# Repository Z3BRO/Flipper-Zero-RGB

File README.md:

# ARCHIVED

Hello everyone! Z3BRO here. It is with great sadness I have to come forward and say that my Flipper Zero RGB Repositories are now dead. 
Instead of dwelling on the fact that its over, I want to thank all the wonderful people who helped me progress as far as I did.

To Rabbitt and Foxx, thank you for your unwavering support through my entire Flipper Zero journey. 
Although it didn't end like we all wished it could have, you will both forever have a special place in my heart. 

To Astro, thank you for everything you did. You know what I'm talking about, thank you for that. I will forever be in your debt. 

To CodeAllNight, thank you for taking this stupid project of mine to the next level. Your selfless acts were not disregarded. 

To the Flipper Zero team, thank you for all your hard work with the Flipper Zero development and the incredible community you've built. 

And finally, I thank all of you! Without the community's support, I would never have been able to do any of this. Thank you. 

# The Future of my RGB Mods

Unfortunately, as you all know, unfortunate circumstances resulted in the termination of my partnership with Rabbit-Labs and the stopping of production. 

But do not fret. I have decided to fully release all the PCB Design Files to my final Internal-RGB and Z3BRgb boards. The KiCad files will be in this repository. 
After some heavy Internal-RGB testing, I made countless changes to the design. These changes eliminate all of the issues with V1 of Internal-RGB and add some new features.

I have removed all licenses from these boards, feel free to distribute, modify, produce and or sell them at your discretion. 

# Flipper Zero RGB

    Big thanks to Quenon#1989, t.me/hitriy, axum#6461, and codeallnight#1337 for making this possible!
This repo is the complilation of all the information avaliable on the Flipper Zero RGB Mods.
# RGB Backlight
Here you can find all the information on the RGB Backlight Mod for the Flipper Zero

## Showcase Video 
- [YouTube](https://youtu.be/W1frMyVFv6Y)
## RGB Backlight Parts

- Capacitors (0.1uF 0603):
  - [Digikey](https://www.digikey.com/en/products/detail/kyocera-avx/06036C104JAT2A/1600414)
- LEDs (SK6805-EC 15):
  - [Digikey](https://www.digikey.com/en/products/detail/adafruit-industries-llc/4492/11569136)
  - [Adafruit](https://www.adafruit.com/product/4492)
  - [Mouser](https://mouser.com/ProductDetail/Adafruit/4492?qs=CUBnOrq4ZJz3oeplDXDOWA%3D%3D)
  - [AliExpress](https://www.aliexpress.us/item/2251832771718100.html)
- Thin gauge wire (36 AWG):
  - [AliExpress](https://www.aliexpress.us/item/3256805268543019.html)

For each Module, you need 3 Capacitors and 3 LEDs

When purchasing Backlight PCBs, ensure the thickness is set to 0.6mm and the layer amount is set to 2.

## Install Guides

- [Updated Guide by Z3BRO](https://github.com/Z3BRO/Flipper-Zero-RGB/blob/main/InternalRGBInstalGuide.md) 

Outdated guides

- [Video Guide by Z3BRO](https://youtu.be/pft1CI5ikA4)
- [Guide by t.me/hitriy](https://telegra.ph/Flipper-Zero-RGB-backlight-guide-12-26)
- [LED Backlight Board Removal Tutorial (Russian)](https://telegra.ph/Izmenenie-cveta-podsvetki-Flipper-Zero-11-14) - Translation may be needed.

## RGB Backlight PCB Assembly

- [Assembly Video](https://youtu.be/N64fDjziTaE)

# Internal RGB
Internal RGB For the Flipper Zero is a mod I have been working on for about a year now.

This mod is for people with a Transparent/Translucent Shell that want their Flippers to be a glowing beacon of light for the Flipper Gods, or they just wanna let you know that their Flipper is cooler than yours because it has gamer lights.

## Where to purchase
The Internal-RGB mod is no longer officially sold nor produced by me. After making these boards open source, people may begin to manufacture and sell them. 

## Supporting Mods
The first batch of Internal RGB Mods will require the user to solder a wire to a Vibro test pad or to the Data Out pad of RGB Backlights that have it (Not all RGB Backlights have a Data Out pad, those that do not are not compatiable with Internal RGB). 

After I placed the order for a production run of Internal RGB I noticed there was a Vibro test pad on the RFID/NFC PCB underneath the mod, on future releases of Internal RGB you will have to option to do a completley wireless install (you will still have to solder the Internal RGB PCB to the RFID/NFC PCB, you just wont need any wires). 

Please note that if you would like to use an RGB Backlight along side your Internal RGB you MUST solder a wire from the RGB Backlight's Data Out pad to the Internal RGB's Data In pad, connecting both the RGB Backlight and Internal RGB to the Vibro line WILL result in issues when changing the color of the LEDs.

## How to install
- [Internal RGB Instal Guide](https://github.com/Z3BRO/Flipper-Zero-RGB/blob/main/InternalRGBInstalGuide.md)

# Supported Firmwares

All repositories below support the RGB Backlight Mod. Only the community modified OFW Supports Internal RGB as of right now.

- **Community Modified**:
  - [OFW (With Internal RGB Support!)](https://github.com/Z3BRO/Flipper-Zero-OFW-RGB)

- **Natively Supported**:
  - [Momentum Firmware](https://github.com/Next-Flip/Momentum-Firmware)
  - [Unleashed Firmware (RGB Specific Build)](https://github.com/DarkFlippers/unleashed-firmware)
  - [RougeMaster Firmware](https://github.com/RogueMaster/flipperzero-firmware-wPlugins)
  - [Xtreme Firmware](https://github.com/Flipper-XFW/Xtreme-Firmware)

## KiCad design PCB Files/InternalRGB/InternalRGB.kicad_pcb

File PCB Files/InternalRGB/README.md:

When ordering, set layer count to 2 and thickness to 0.1mm. Make sure you are ordering Flex PCBs.

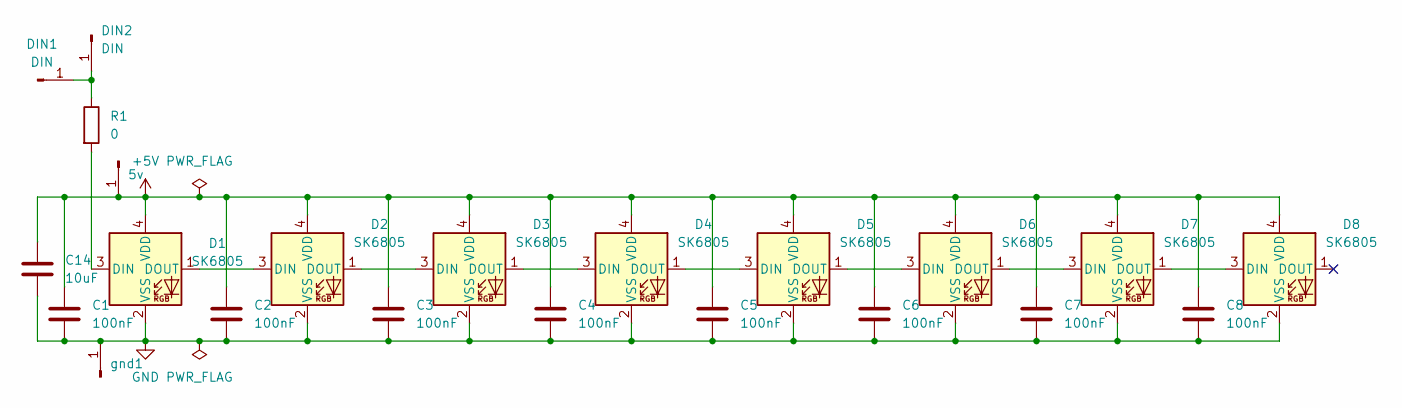
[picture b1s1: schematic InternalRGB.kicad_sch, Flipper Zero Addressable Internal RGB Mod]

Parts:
5v1: 5v; PinHeader_1x01_P2.54mm_Vertical
C1, C2, C3, C4, C5, C6, C7, C8: 100nF; C_0402_1005Metric
C14: 10uF; C_0402_1005Metric
D1, D2, D3, D4, D5, D6, D7, D8: SK6805; LED_SK6812_EC15_1.5x1.5mm
DIN1: DIN; SolderWirePad_1x01_SMD_1x2mm
DIN2: DIN; PinHeader_1x01_P2.54mm_Vertical
R1: 0; R_0402_1005Metric
gnd1: gnd; PinHeader_1x01_P2.54mm_Vertical

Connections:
+5V: 5v1.1, C1.1, C2.1, C3.1, C4.1, C5.1, C6.1, C7.1, C8.1, C14.1, D1.4 (VDD), D2.4 (VDD), D3.4 (VDD), D4.4 (VDD), D5.4 (VDD), D6.4 (VDD), D7.4 (VDD), D8.4 (VDD)
GND: C1.2, C2.2, C3.2, C4.2, C5.2, C6.2, C7.2, C8.2, C14.2, D1.2 (VSS), D2.2 (VSS), D3.2 (VSS), D4.2 (VSS), D5.2 (VSS), D6.2 (VSS), D7.2 (VSS), D8.2 (VSS), gnd1.1; also elsewhere on the board
unnamed: D1.3 (DIN), R1.2
unnamed: D1.1 (DOUT), D2.3 (DIN)
unnamed: D2.1 (DOUT), D3.3 (DIN)
unnamed: D3.1 (DOUT), D4.3 (DIN)
unnamed: D4.1 (DOUT), D5.3 (DIN)
unnamed: D5.1 (DOUT), D6.3 (DIN)
unnamed: D6.1 (DOUT), D7.3 (DIN)
unnamed: D7.1 (DOUT), D8.3 (DIN)
unnamed 10: DIN1.1, DIN2.1, R1.1; also elsewhere on the board

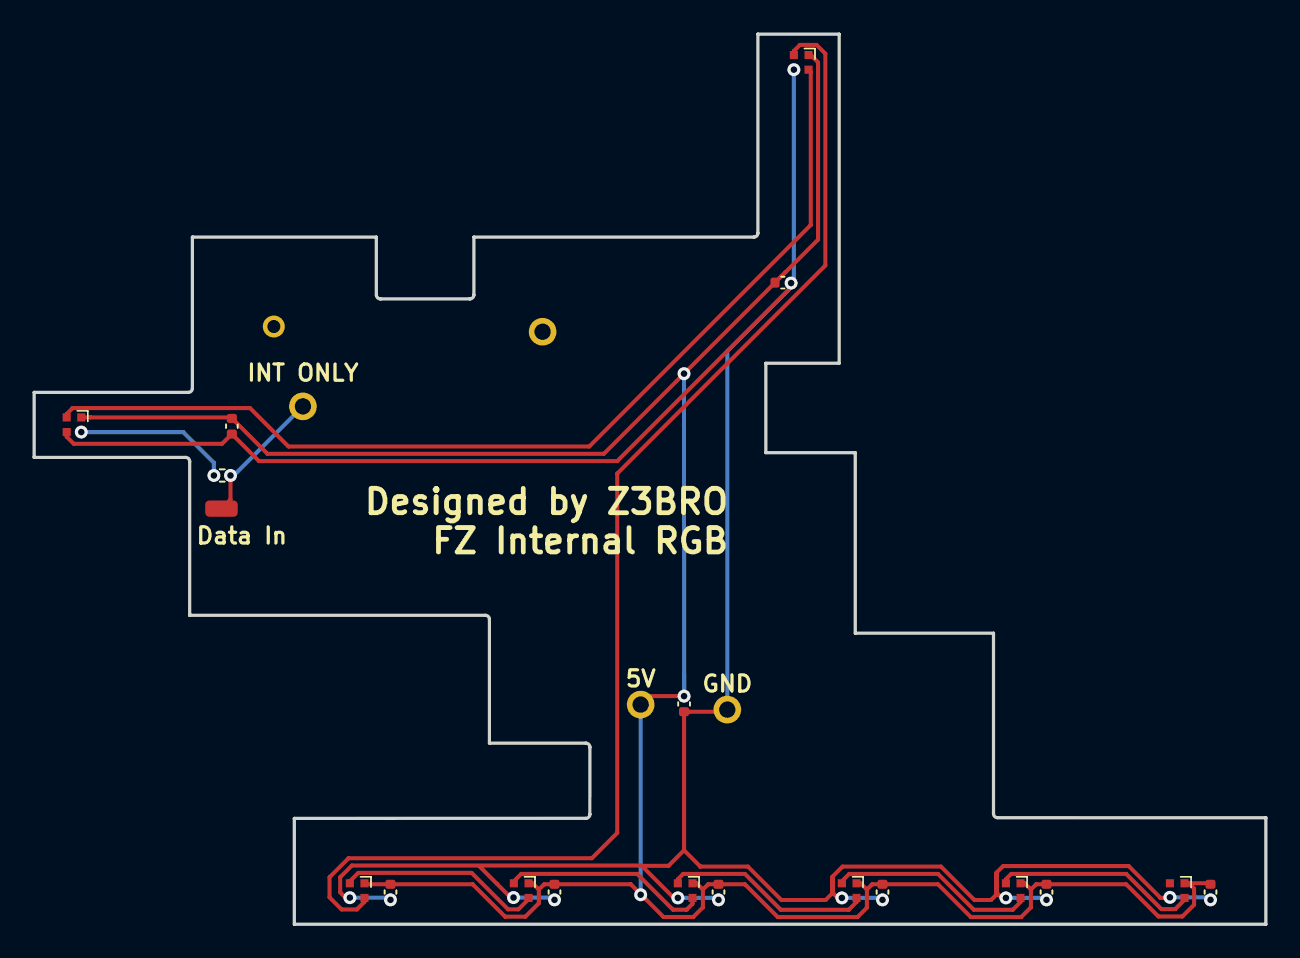
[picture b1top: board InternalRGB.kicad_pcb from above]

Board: 2 copper layers, 75.8 x 54.7 mm, 23 parts (0 on the bottom side), 11 nets.

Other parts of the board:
INT ONLY: DIN; PinHeader_1x01_P2.54mm_Vertical
gnd2: GND; PinHeader_1x01_P2.54mm_Vertical

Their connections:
GND: gnd2.1; also elsewhere on the board
unnamed 10: INT ONLY.1; also elsewhere on the board

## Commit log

2022-12-27 Added Files
2022-12-27 Created a readme.md
2022-12-28 Updated .Patch File
2022-12-28 Updated
    Added working patch files and update files.
2023-01-13 Updated PCB
2023-01-14 Updated Files
    Updated update files
2023-01-19 Updated
    Updated for Vibro Internal line
2023-02-02 Updated Patch
2023-03-10 Organized RGB FW FILES
2023-03-18 Software : Better/More Color WS2812B.c
    Colors in order
    Orange
    Red
    Maroon
    Yellow
    Olive
2023-03-18 Software : Better/More Color rgb_backlight.c
    Colors in order
    Orange
    Red
    Maroon
    Yellow
    Olive
2023-03-18 Fixing your shitty HTML
    sorry
2023-03-19 html fix
2023-03-21 fixing orange
2023-03-21 Fixy Update FIles
    Sowee
2023-03-21 Moved stuff
2023-03-22 new pink & fixed white RGB
2023-03-24 Simplify firmware patches, remove old unused code
2023-03-24 remove unused file
    handled via rgb_backlight.c
2023-03-24 remove unused file
    handled via rgb_backlight.h
2023-05-08 Fixing Dex's stuff
2023-06-13 fixed occasional backlight issues & implemented stealth mode support
2023-08-03 Updating pretty much everything
    Huge thanks to xMasterX for rewriting the rgb patch.
2023-10-30 Update RGB_FW.patch
    fixed directory for moved file
2023-10-31 moving files around
2023-11-10 Update README.md
    - removed the "How to compile" section since thats mostly already explained and maintained in the Firmware repositories.
    - Made everything clean
    - Added Xtreme Firmware (very good support for RGB Mod)
2024-01-09 Remove Things
2024-01-09 Move gerber
2025-01-18 Final Readme.md Update
2025-01-18 Thats it, goodbye everyone.
